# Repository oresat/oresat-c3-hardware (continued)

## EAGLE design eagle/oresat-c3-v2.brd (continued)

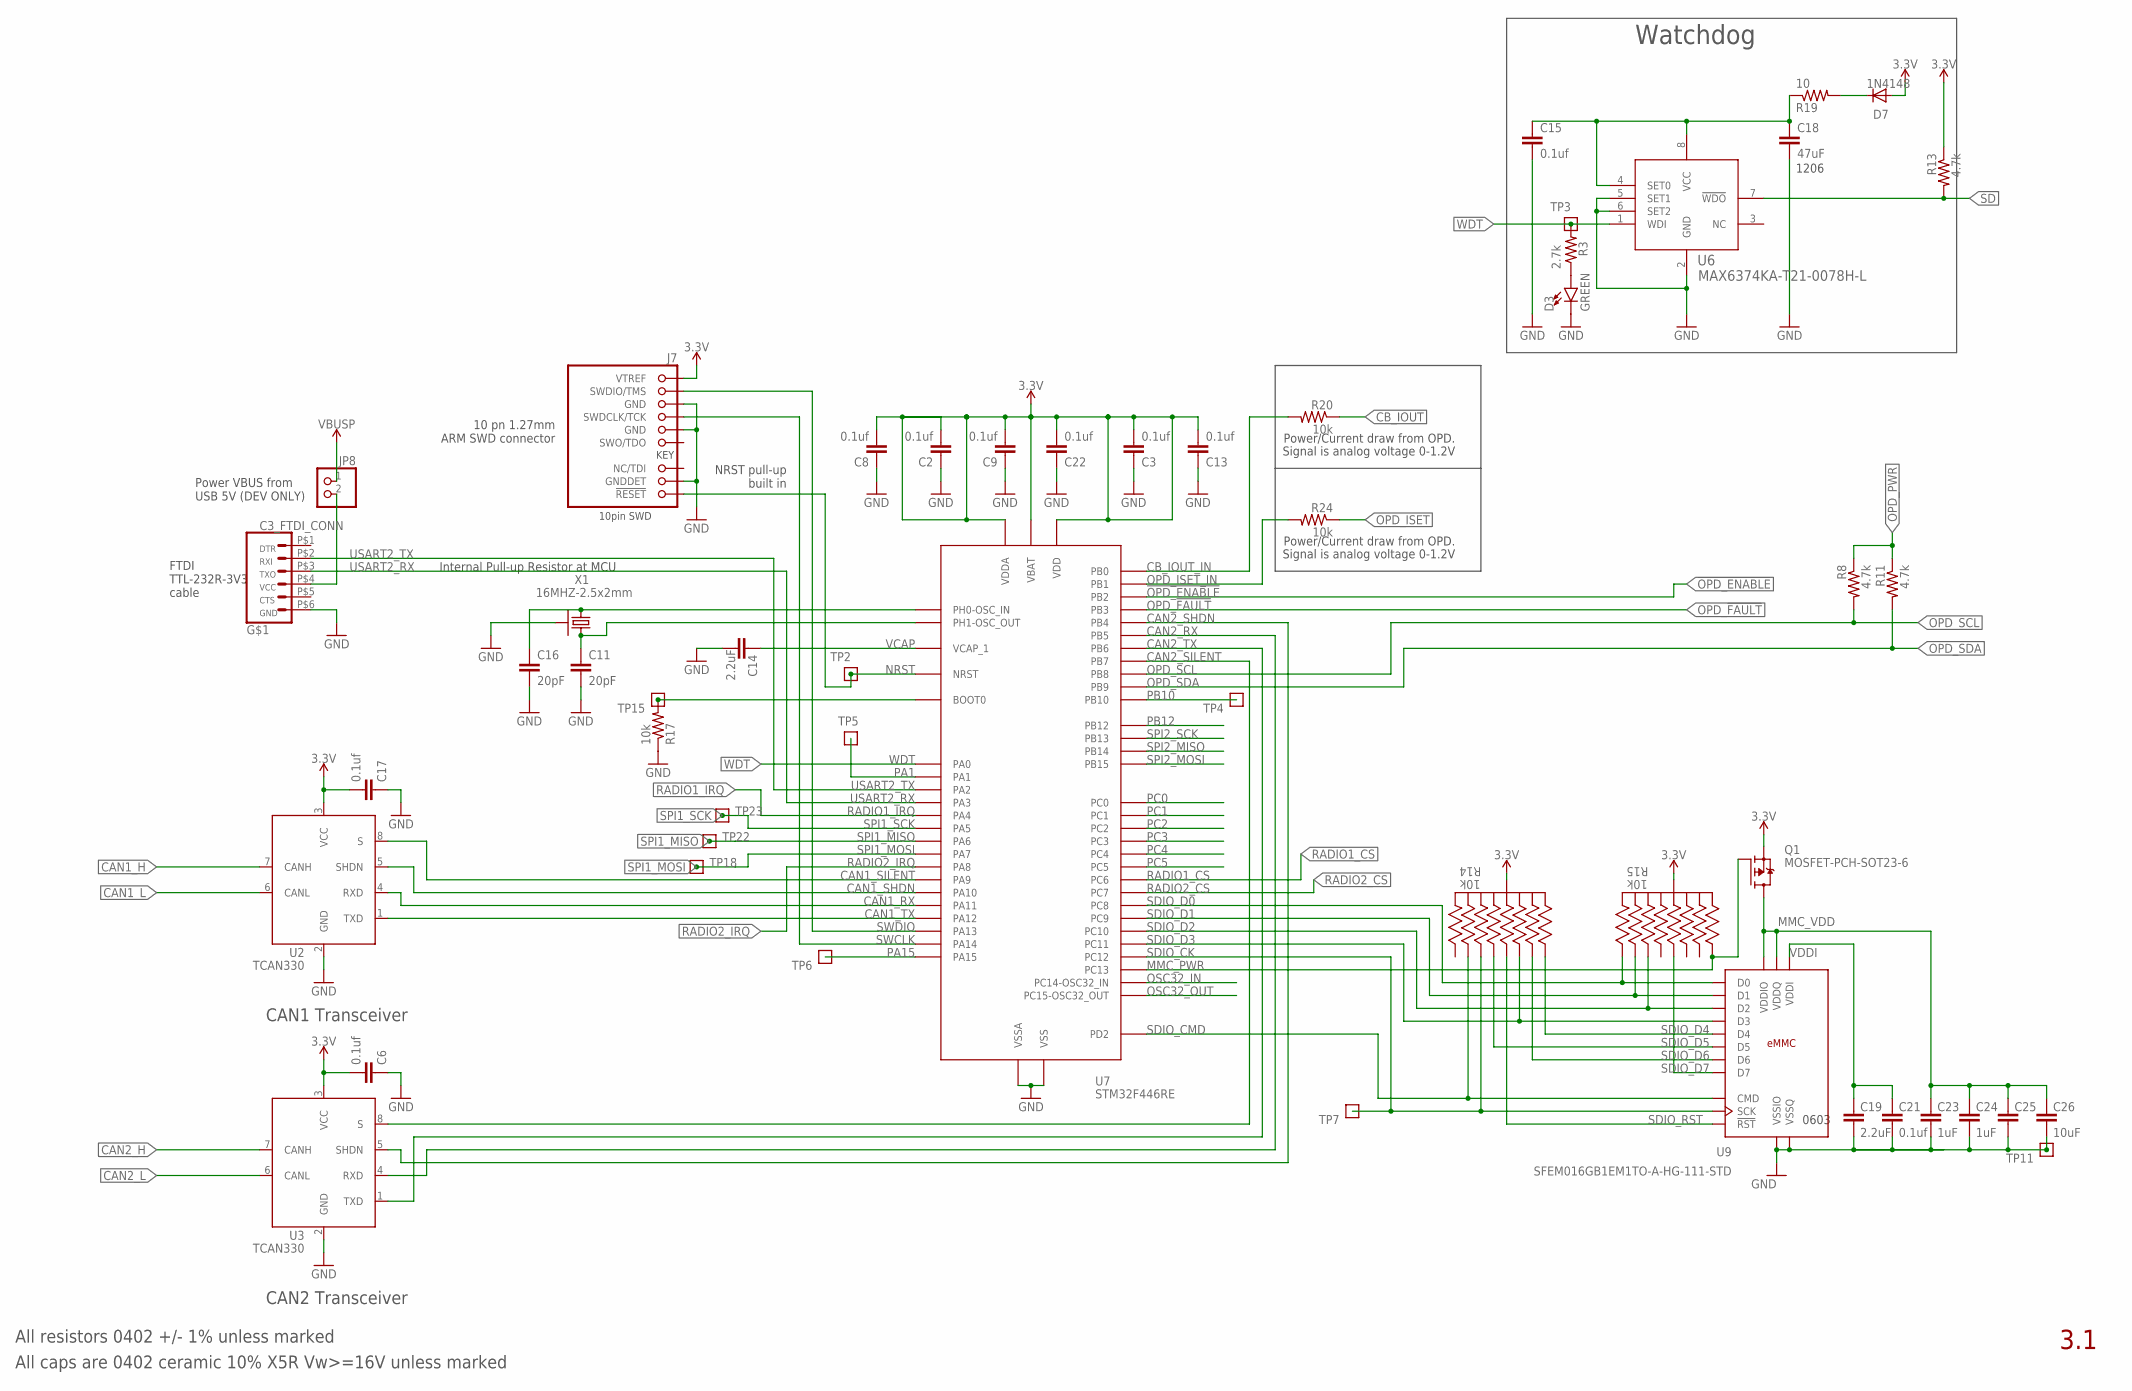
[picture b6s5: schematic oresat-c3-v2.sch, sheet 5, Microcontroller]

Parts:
C2, C3, C6, C8, C9, C13, C17, C21, C22: 0.1uf; .0603-B-NOSILK; MPN CL05B104KO5NNNC
C11, C16: 20pF; .0603-B-NOSILK; MPN CL05C200JB51PNC
C14, C19: 2.2uF; .0603-B-NOSILK; MPN CL05B104KO5NNNC
C15: 0.1uf; .0603-B-NOSILK; MPN CL05C200JB51PNC
C18: 47uF; .0603-B-NOSILK; MPN CL05C200JB51PNC
C23, C24, C25: 1uF; .0603-B-NOSILK; MPN CL05B104KO5NNNC
C26: 10uF; .0603-B-NOSILK; MPN CL05B104KO5NNNC
D3: GREEN; LED-0603
D7: 1N4148; SOD-323
J7: FTSH-105-XX-X-DV-K; CON10_2X5_DUK_FTSH; MPN FTSH-105-01-F-DV-K
JP8: PINHD-1X2; 1X02
Q1: MOSFET-PCH-SOT23-6; SOT23-6
R3: 2.7k; .0603-C-NOSILK; MPN RC1005F6653CS
R8, R11, R13: 4.7k; .0603-C-NOSILK
R14, R15: 10k; ARRAY_EXBA-M
R17: 10k; .0603-C-NOSILK; MPN RC1005F6653CS
R19: 10; .0603-C-NOSILK
R20, R24: 10k; .0603-C-NOSILK
TP2, TP3, TP4, TP5, TP6, TP7, TP11, TP15, TP18, TP22, TP23: TEST-POINT; 2MM-TEST-POINT
U2, U3: TCAN330; SOT23-8_TI-DCN; MPN TCAN330GDCNT
U6: MAX6374KA-T21-0078H-L; 21-0078H-L
U7: STM32F446RE; QFP-10X10-64
U9: SFEM016GB1EM1TO-A-HG-111-STD; BGA-153(11.5X13)(EMMC-BA)
U$2: C3_FTDI_CONN; 6_PIN_SERIAL_TARGET_SIDE_W_SILK
X1: 16MHZ-2.5x2mm; CRYSTAL_2.5X2; MPN ECS-160-10-36Q-ES-TR

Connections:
3.3V: C2.2, C3.2, C6.2, C8.2, C9.2, C13.2, C17.2, C22.2, D7.2 (A), J7.1 (VTREF), Q1.4 (S), R13.1, R14.5 (55), R14.10 (55), R15.5 (55), R15.10 (55), U2.3 (VCC), U3.3 (VCC), U7.1 (VBAT), U7.13 (VDDA), U7.19 (VDD), U7.32 (VDD), U7.48 (VDD), U7.64 (VDD); also elsewhere on the board
!OPD_ENABLE: U7.28 (PB2); also elsewhere on the board
BOOT0: R17.2, TP15.1, U7.60 (BOOT0)
CAN1_H: U2.7 (CANH); also elsewhere on the board
CAN1_L: U2.6 (CANL); also elsewhere on the board
CAN1_RX: U2.4 (RXD), U7.44 (PA11)
CAN1_SHDN: U2.5 (SHDN), U7.43 (PA10)
CAN1_SILENT: U2.8 (S), U7.42 (PA9)
CAN1_TX: U2.1 (TXD), U7.45 (PA12)
CAN2_H: U3.7 (CANH); also elsewhere on the board
CAN2_L: U3.6 (CANL); also elsewhere on the board
CAN2_RX: U3.4 (RXD), U7.57 (PB5)
CAN2_SHDN: U3.5 (SHDN), U7.56 (PB4)
CAN2_SILENT: U3.8 (S), U7.59 (PB7)
CAN2_TX: U3.1 (TXD), U7.58 (PB6)
CB_IOUT: R20.1; also elsewhere on the board
CB_IOUT_IN: R20.2, U7.26 (PB0)
CRYSTALIN: C16.1, U7.5 (PH0-OSC_IN), X1.1
CRYSTALOUT: C11.1, U7.6 (PH1-OSC_OUT), X1.3 (2)
GND: C2.1, C3.1, C6.1, C8.1, C9.1, C11.2, C13.1, C14.2, C15.2, C16.2, C17.1, C18.2, C19.2, C21.2, C22.1, C23.2, C24.2, C25.2, C26.2, D3.C, J7.3 (GND), J7.5 (GND), J7.9 (GNDDET), R17.1, TP11.1, U2.2 (GND), U3.2 (GND), U6.2 (GND), U6.5 (SET1), U6.6 (SET2), U7.12 (VSSA), U7.18 (VSS), U7.31 (VSS), U7.47 (VSS), U7.63 (VSS), U9.A6 (VSSIO), U9.C4 (VSSQ), U9.D4 (VSSIO), U9.E7 (VSSIO), U9.G5 (VSSIO), U9.H10 (VSSIO), U9.J5 (VSSIO), U9.K8 (VSSIO), U9.N1 (VSSQ), U9.N2 (VSSQ), U9.N5 (VSSQ), U9.P4 (VSSQ), U9.P6 (VSSQ), U$2.P$6 (GND), X1.2 (SHIELD), X1.4 (SHIELD); also elsewhere on the board
MMC_PWR: Q1.3 (G), R15.6 (66), U7.2 (PC13)
MMC_VDD: C23.1, C24.1, C25.1, C26.1, Q1.1 (D), Q1.2 (D), Q1.5 (D), Q1.6 (D), U9.C6 (VDDQ), U9.E6 (VDDIO), U9.F5 (VDDIO), U9.J10 (VDDIO), U9.K9 (VDDIO), U9.M4 (VDDQ), U9.N4 (VDDQ), U9.P3 (VDDQ), U9.P5 (VDDQ)
unnamed: D3.A, R3.1
unnamed: D7.1 (C), R19.2
unnamed: JP8.2, U$2.P$4 (VCC)
NRST: J7.10 (!RESET), TP2.1, U7.7 (NRST)
OPD_!FAULT: U7.55 (PB3); also elsewhere on the board
OPD_ISET: R24.1; also elsewhere on the board
OPD_ISET_IN: R24.2, U7.27 (PB1)
OPD_PWR: R8.1, R11.1; also elsewhere on the board
OPD_SCL: R8.2, U7.61 (PB8); also elsewhere on the board
OPD_SDA: R11.2, U7.62 (PB9); also elsewhere on the board
OSC32_IN: U7.3 (PC14-OSC32_IN)
OSC32_OUT: U7.4 (PC15-OSC32_OUT)
PA1: TP5.1, U7.15 (PA1)
PA15: TP6.1, U7.50 (PA15)
PB10: TP4.1, U7.29 (PB10)
PB12: U7.33 (PB12)
PC0: U7.8 (PC0)
PC1: U7.9 (PC1)
PC2: U7.10 (PC2)
PC3: U7.11 (PC3)
PC4: U7.24 (PC4)
PC5: U7.25 (PC5)
RADIO1_CS: U7.37 (PC6); also elsewhere on the board
RADIO1_IRQ: U7.20 (PA4); also elsewhere on the board
RADIO2_CS: U7.38 (PC7); also elsewhere on the board
RADIO2_IRQ: U7.41 (PA8); also elsewhere on the board
SD: R13.2, U6.7 (!WDO); also elsewhere on the board
SDIO_CK: R14.2 (22), TP7.1, U7.53 (PC12), U9.M6 (SCK)
SDIO_CMD: R14.9 (99), U7.54 (PD2), U9.M5 (CMD)
SDIO_D0: R15.1 (11), U7.39 (PC8), U9.A3 (D0)
SDIO_D1: R15.9 (99), U7.40 (PC9), U9.A4 (D1)
SDIO_D2: R15.2 (22), U7.51 (PC10), U9.A5 (D2)
SDIO_D3: R14.7 (77), U7.52 (PC11), U9.A1 (D3), U9.B2 (D3)
SDIO_D4: R14.6 (66), U9.A2 (D4), U9.B3 (D4)
SDIO_D5: R14.8 (88), U9.B4 (D5), U9.C3 (D5), U9.D3 (D5)
SDIO_D6: R14.4 (44), U9.B5 (D6), U9.C5 (D6)
SDIO_D7: R15.3 (33), U9.B6 (D7), U9.C7 (D7)
SDIO_RST: R14.3 (33), U9.K5 (!RST!)
SPI1_MISO: TP22.1, U7.22 (PA6); also elsewhere on the board
SPI1_MOSI: TP18.1, U7.23 (PA7); also elsewhere on the board
SPI1_SCK: TP23.1, U7.21 (PA5); also elsewhere on the board
SPI2_MISO: U7.35 (PB14)
SPI2_MOSI: U7.36 (PB15)
SPI2_SCK: U7.34 (PB13)
SWCLK: J7.4 (SWDCLK/TCK), U7.49 (PA14)
SWDIO: J7.2 (SWDIO/TMS), U7.46 (PA13)
USART2_RX: U7.17 (PA3), U$2.P$3 (TXO)
USART2_TX: U7.16 (PA2), U$2.P$2 (RXI)
VBUSP: JP8.1; also elsewhere on the board
VCAP: C14.1, U7.30 (VCAP_1)
VDDI: C19.1, C21.1, U9.C1 (VDDI), U9.C2 (VDDI)
WDT: R3.2, TP3.1, U6.1 (WDI), U7.14 (PA0)
WDT-PWR: C15.1, C18.1, R19.1, U6.4 (SET0), U6.8 (VCC)

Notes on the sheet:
NRST pull-up built in
FTDI TTL-232R-3V3 cable
Power VBUS from USB 5V (DEV ONLY)
10 pn 1.27mm ARM SWD connector
CAN1 Transceiver
3.1
Power/Current draw from OPD.
Signal is analog voltage 0-1.2V
CAN2 Transceiver
Watchdog
Internal Pull-up Resistor at MCU
All resistors 0402 +/- 1% unless marked
All caps are 0402 ceramic 10% X5R Vw>=16V unless marked
1206
0603

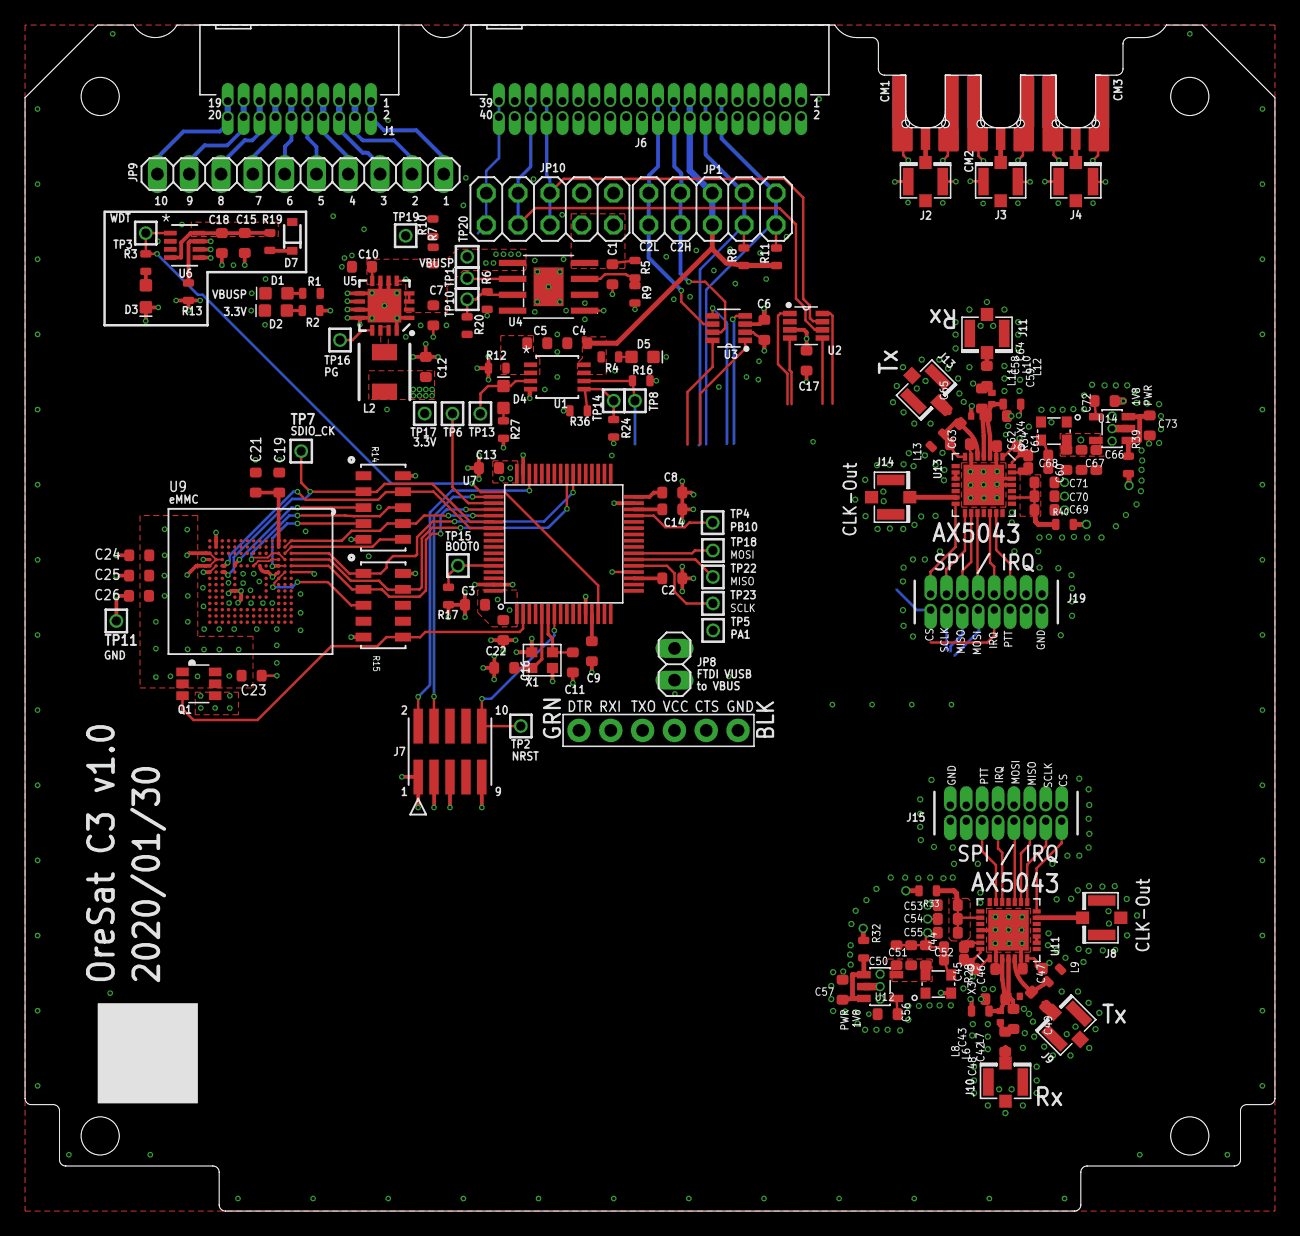
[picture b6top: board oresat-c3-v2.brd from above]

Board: 4 copper layers, 99.8 x 94.7 mm, 163 parts (0 on the bottom side), 133 nets.

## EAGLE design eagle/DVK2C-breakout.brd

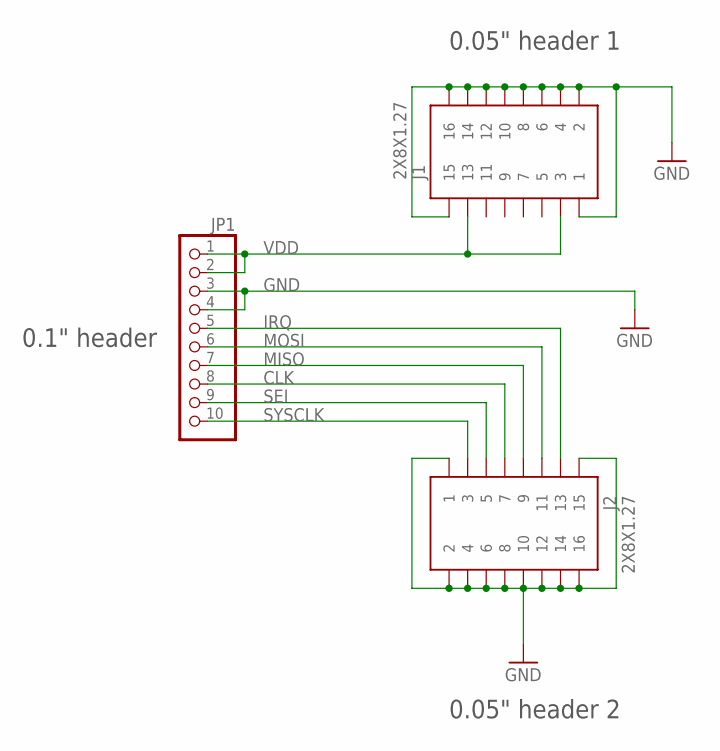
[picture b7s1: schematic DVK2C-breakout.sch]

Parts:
J1, J2: 2X8X1.27
JP1: PINHD-1X10; 1X10

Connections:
CLK: J2.7, JP1.8
GND: J1.1, J1.2, J1.4, J1.6, J1.8, J1.10, J1.12, J1.14, J1.15, J1.16, J2.1, J2.2, J2.4, J2.6, J2.8, J2.10, J2.12, J2.14, J2.15, J2.16, JP1.3, JP1.4
IRQ: J2.13, JP1.5
MISO: J2.9, JP1.7
MOSI: J2.11, JP1.6
SEI: J2.5, JP1.9
SYSCLK: J2.3, JP1.10
VDD: J1.3, J1.13, JP1.1, JP1.2

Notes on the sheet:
0.1" header
0.05" header 1
0.05" header 2

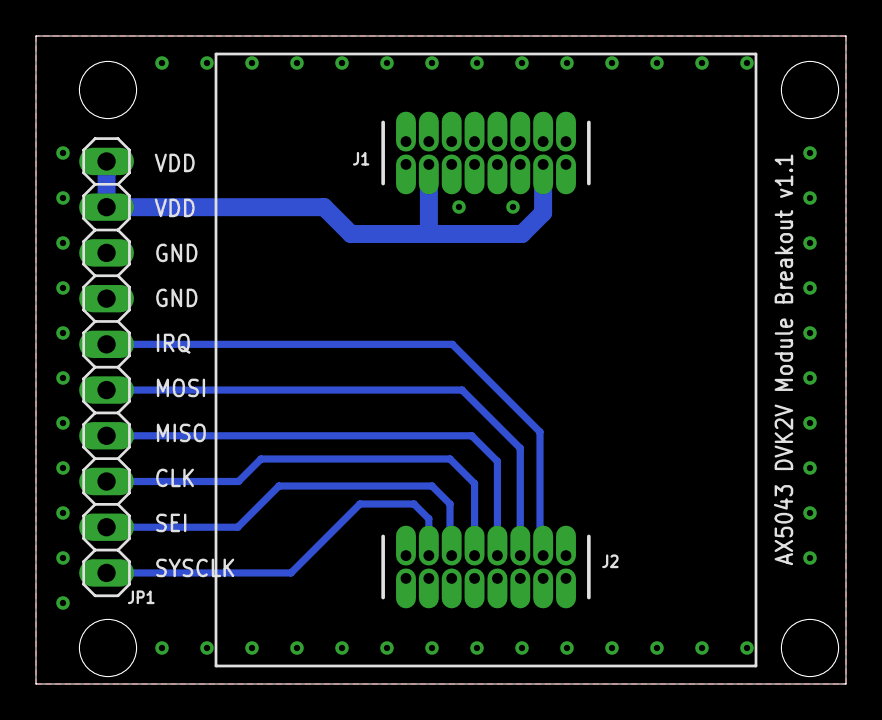
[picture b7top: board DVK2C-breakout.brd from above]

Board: 2 copper layers, 45.0 x 36.0 mm, 3 parts (0 on the bottom side), 8 nets.

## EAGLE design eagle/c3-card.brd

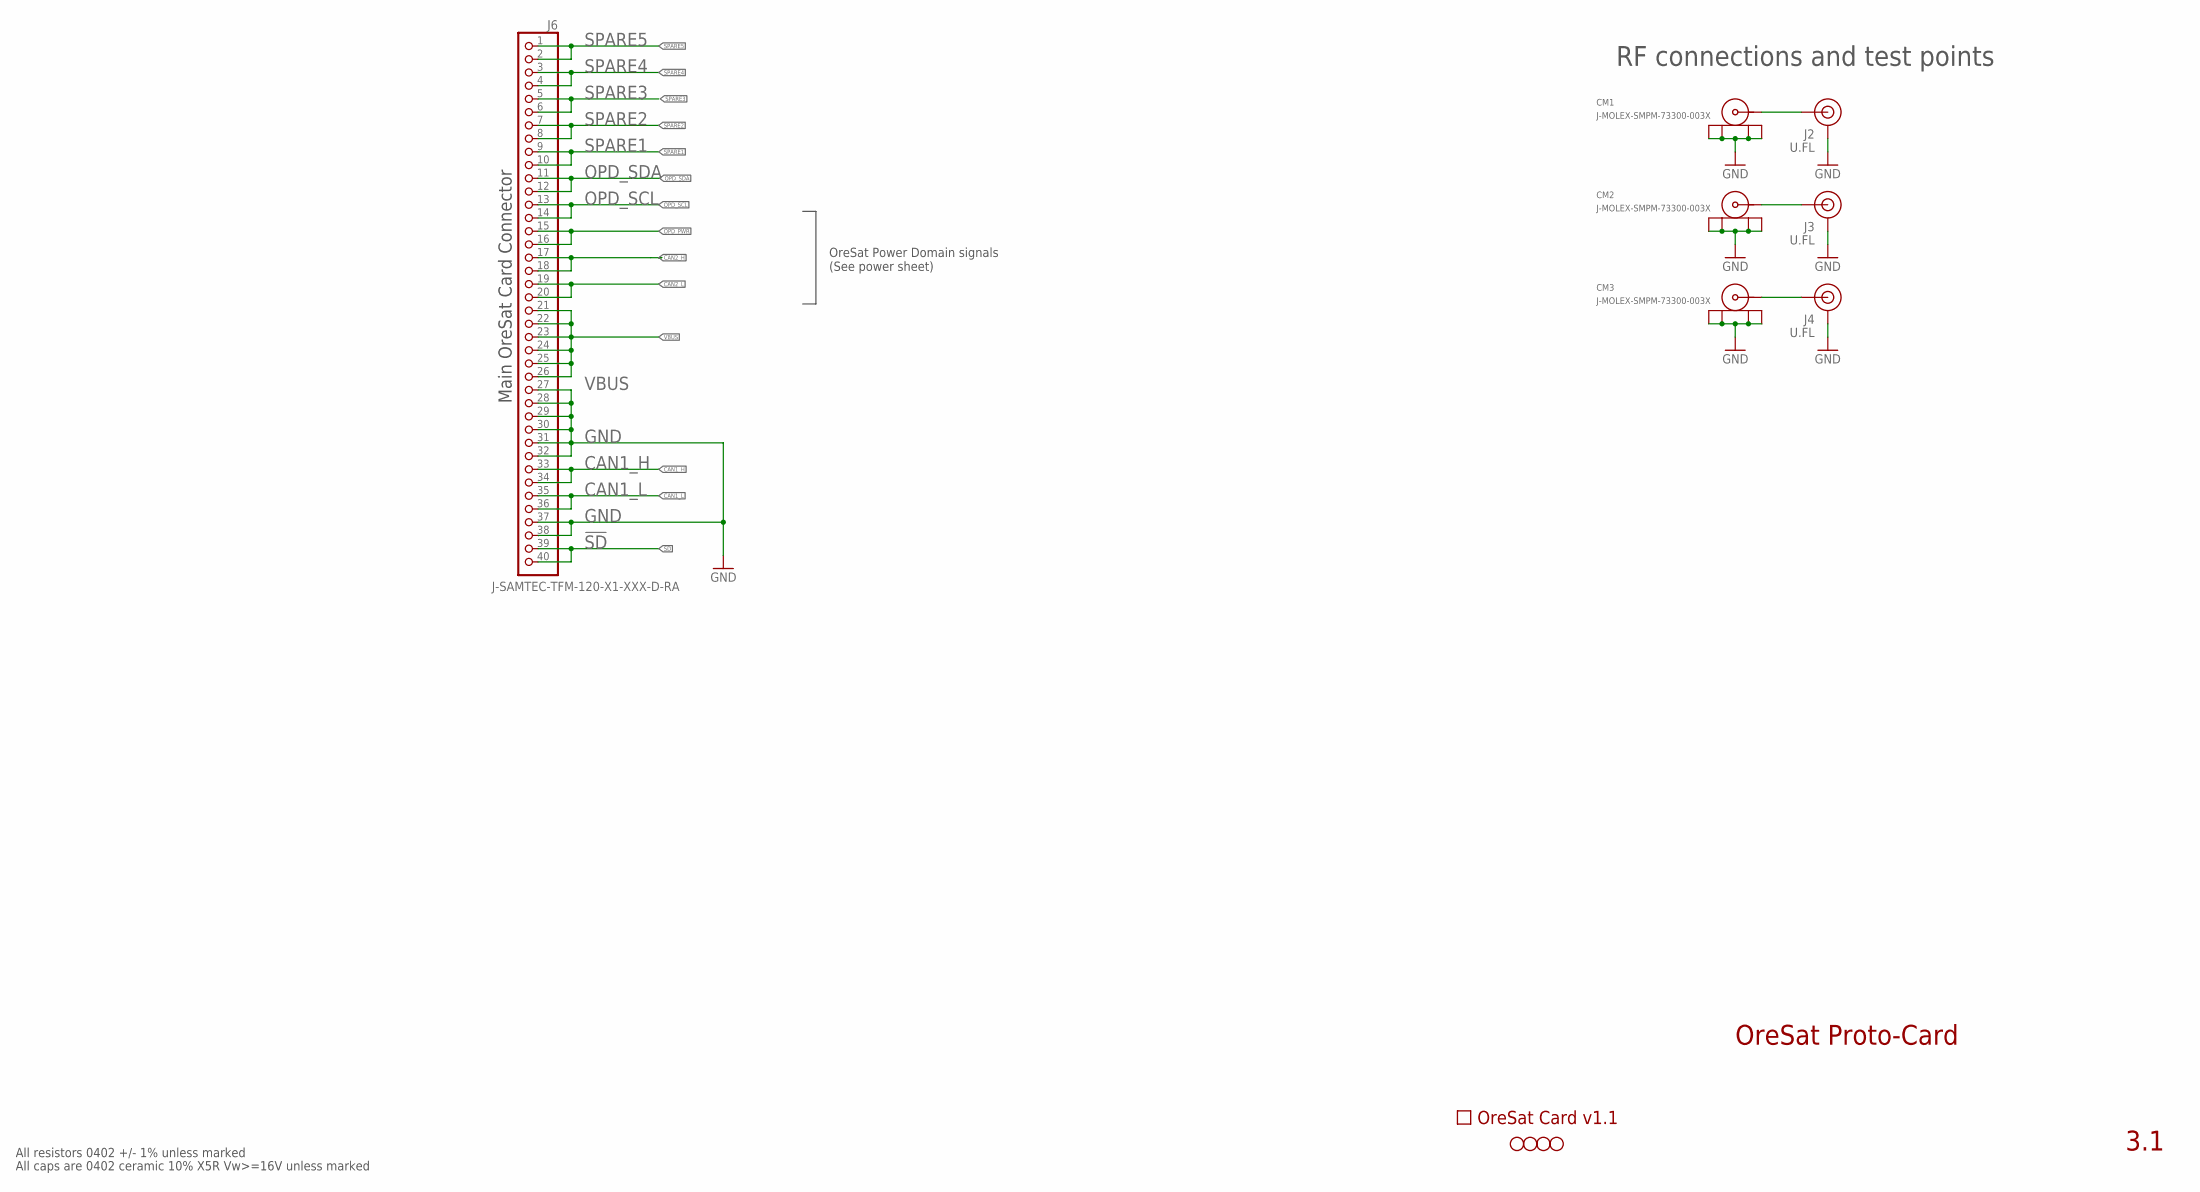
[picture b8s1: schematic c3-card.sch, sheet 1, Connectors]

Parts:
CM1, CM2, CM3: J-MOLEX-SMPM-73300-003X; J-MOLEX-SMPM-073300-003X; MPN 73300-0020
H1, H2, H3, H4: STAND-OFFTIGHT; STAND-OFF-TIGHT
J2, J3, J4: U.FL
J6: J-SAMTEC-TFM-120-X1-XXX-D-RA; MPN TFM-120-01-L-D-RA
U$2: ORESAT-CARD-V1.1-3XRF

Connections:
!SD: J6.39, J6.40
CAN1_H: J6.33, J6.34; also elsewhere on the board
CAN1_L: J6.35, J6.36; also elsewhere on the board
CAN2_H: J6.17, J6.18; also elsewhere on the board
CAN2_L: J6.19, J6.20; also elsewhere on the board
GND: CM1.P$1 (SHIELD3), CM1.P$2 (SHIELD2), CM1.P$3 (SHIELD1), CM1.P$4 (SHIELD), CM2.P$1 (SHIELD3), CM2.P$2 (SHIELD2), CM2.P$3 (SHIELD1), CM2.P$4 (SHIELD), CM3.P$1 (SHIELD3), CM3.P$2 (SHIELD2), CM3.P$3 (SHIELD1), CM3.P$4 (SHIELD), J2.1 (GND), J2.2 (GND), J3.1 (GND), J3.2 (GND), J4.1 (GND), J4.2 (GND), J6.27, J6.28, J6.29, J6.30, J6.31, J6.32, J6.37, J6.38; also elsewhere on the board
unnamed: CM3.RF (CENTER), J4.FEED (SIGNAL)
OPD_PWR: J6.15, J6.16
OPD_SCL: J6.13, J6.14
OPD_SDA: J6.11, J6.12
RF1: CM1.RF (CENTER), J2.FEED (SIGNAL)
RF2: CM2.RF (CENTER), J3.FEED (SIGNAL)
SPARE1: J6.9, J6.10
SPARE2: J6.7, J6.8
SPARE3: J6.5, J6.6
SPARE4: J6.3, J6.4
SPARE5: J6.1, J6.2
VBUS: J6.21, J6.22, J6.23, J6.24, J6.25, J6.26; also elsewhere on the board

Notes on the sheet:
OreSat Proto-Card
3.1
All resistors 0402 +/- 1% unless marked
All caps are 0402 ceramic 10% X5R Vw>=16V unless marked
Main OreSat Card Connector
RF connections and test points
OreSat Power Domain signals (See power sheet)

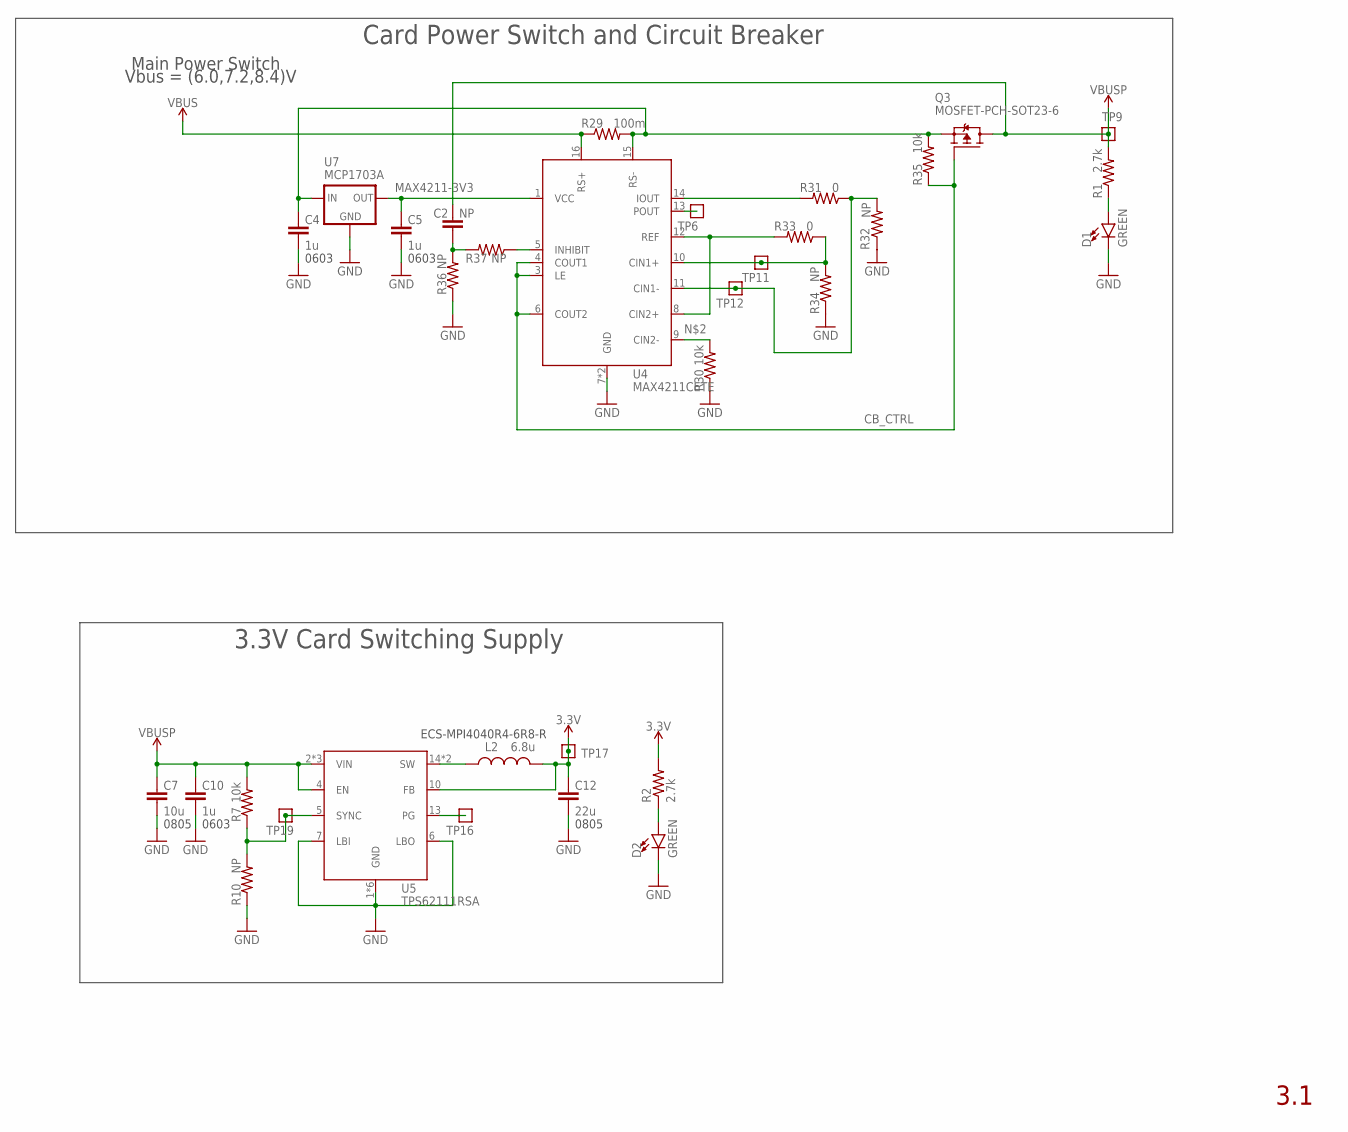
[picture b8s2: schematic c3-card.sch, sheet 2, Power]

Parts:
C2: NP; .0402-B-NOSILK; MPN CL05B104KO5NNNC
C4, C5, C10: 1u; .0603-B-NOSILK; MPN CL05B104KO5NNNC
C7: 10u; .0805-B-NOSILK
C12: 22u; .0805-B-NOSILK
D1, D2: GREEN; LED-0603
L2: 6.8u; ECS-MPI4040; MPN ECS-MPI4040R4-6R8-R
Q3: MOSFET-PCH-SOT23-6; SOT23-6; MPN DMP3050LVT-7
R1, R2: 2.7k; .0402-B-NOSILK; MPN RC1005F6653CS
R7, R30, R35: 10k; .0402-B-NOSILK; MPN RC1005F6653CS
R10, R32, R34, R36, R37: NP; .0402-B-NOSILK; MPN RC1005F6653CS
R29: 100m; R1206
R31, R33: 0; .0402-B-NOSILK; MPN RC1005F6653CS
TP6, TP9, TP11, TP12, TP16, TP17, TP19: TEST-POINT; 2MM-TEST-POINT
U4: MAX4211CETE; QFN65P400X400X80-17T210; MPN MAX4211CETE
U5: TPS62111RSA; S-PVQFN-16; MPN TPS62111RSA
U7: MCP1703A; SOT23; MPN MCP1703AT-3302E/CB

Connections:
3.3V: C12.1, L2.2, R2.2, TP17.1, U5.10 (FB); also elsewhere on the board
CB_CTRL: Q3.3 (G), R35.1, U4.3 (LE), U4.4 (COUT1), U4.6 (COUT2)
GND: C4.2, C5.2, C7.2, C10.2, C12.2, D1.C, D2.C, R10.1, R30.1, R32.1, R34.1, R36.1, U4.7 (GND), U4.EPAD (GND), U5.1 (GND), U5.6 (LBO), U5.7 (LBI), U5.9 (GND), U5.11 (GND), U5.12 (GND), U5.16 (GND), U5.PAD (GND), U7.1 (GND); also elsewhere on the board
MAX4211-3V3: C5.1, U4.1 (VCC), U7.2 (OUT)
unnamed: R30.2, U4.9 (CIN2-)
unnamed: D1.A, R1.1
unnamed: D2.A, R2.1
unnamed: C4.1, Q3.4 (S), R29.2, R35.2, U4.15 (RS-), U7.3 (IN)
unnamed: R31.1, R32.2, TP12.1, U4.11 (CIN1-)
unnamed: R33.1, R34.2, TP11.1, U4.10 (CIN1+)
unnamed: R31.2, U4.14 (IOUT)
unnamed: R33.2, U4.8 (CIN2+), U4.12 (REF)
unnamed: TP6.1, U4.13 (POUT)
unnamed: C2.1, R36.2, R37.2
unnamed: R37.1, U4.5 (INHIBIT)
TPS62111-PG: TP16.1, U5.13 (PG)
TPS62111-SYNC: R7.1, R10.2, TP19.1, U5.5 (SYNC)
TPS62111_SW: L2.1, U5.14 (SW), U5.15 (SW)
VBUS: R29.1, U4.16 (RS+); also elsewhere on the board
VBUSP: C2.2, C7.1, C10.1, Q3.1 (D), Q3.2 (D), Q3.5 (D), Q3.6 (D), R1.2, R7.2, TP9.1, U5.2 (VIN), U5.3 (VIN), U5.4 (EN), U5.8 (VIN)

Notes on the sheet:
Main Power Switch
0805
0603
ECS-MPI4040R4-6R8-R
Vbus = (6.0,7.2,8.4)V
3.3V Card Switching Supply
Card Power Switch and Circuit Breaker
3.1

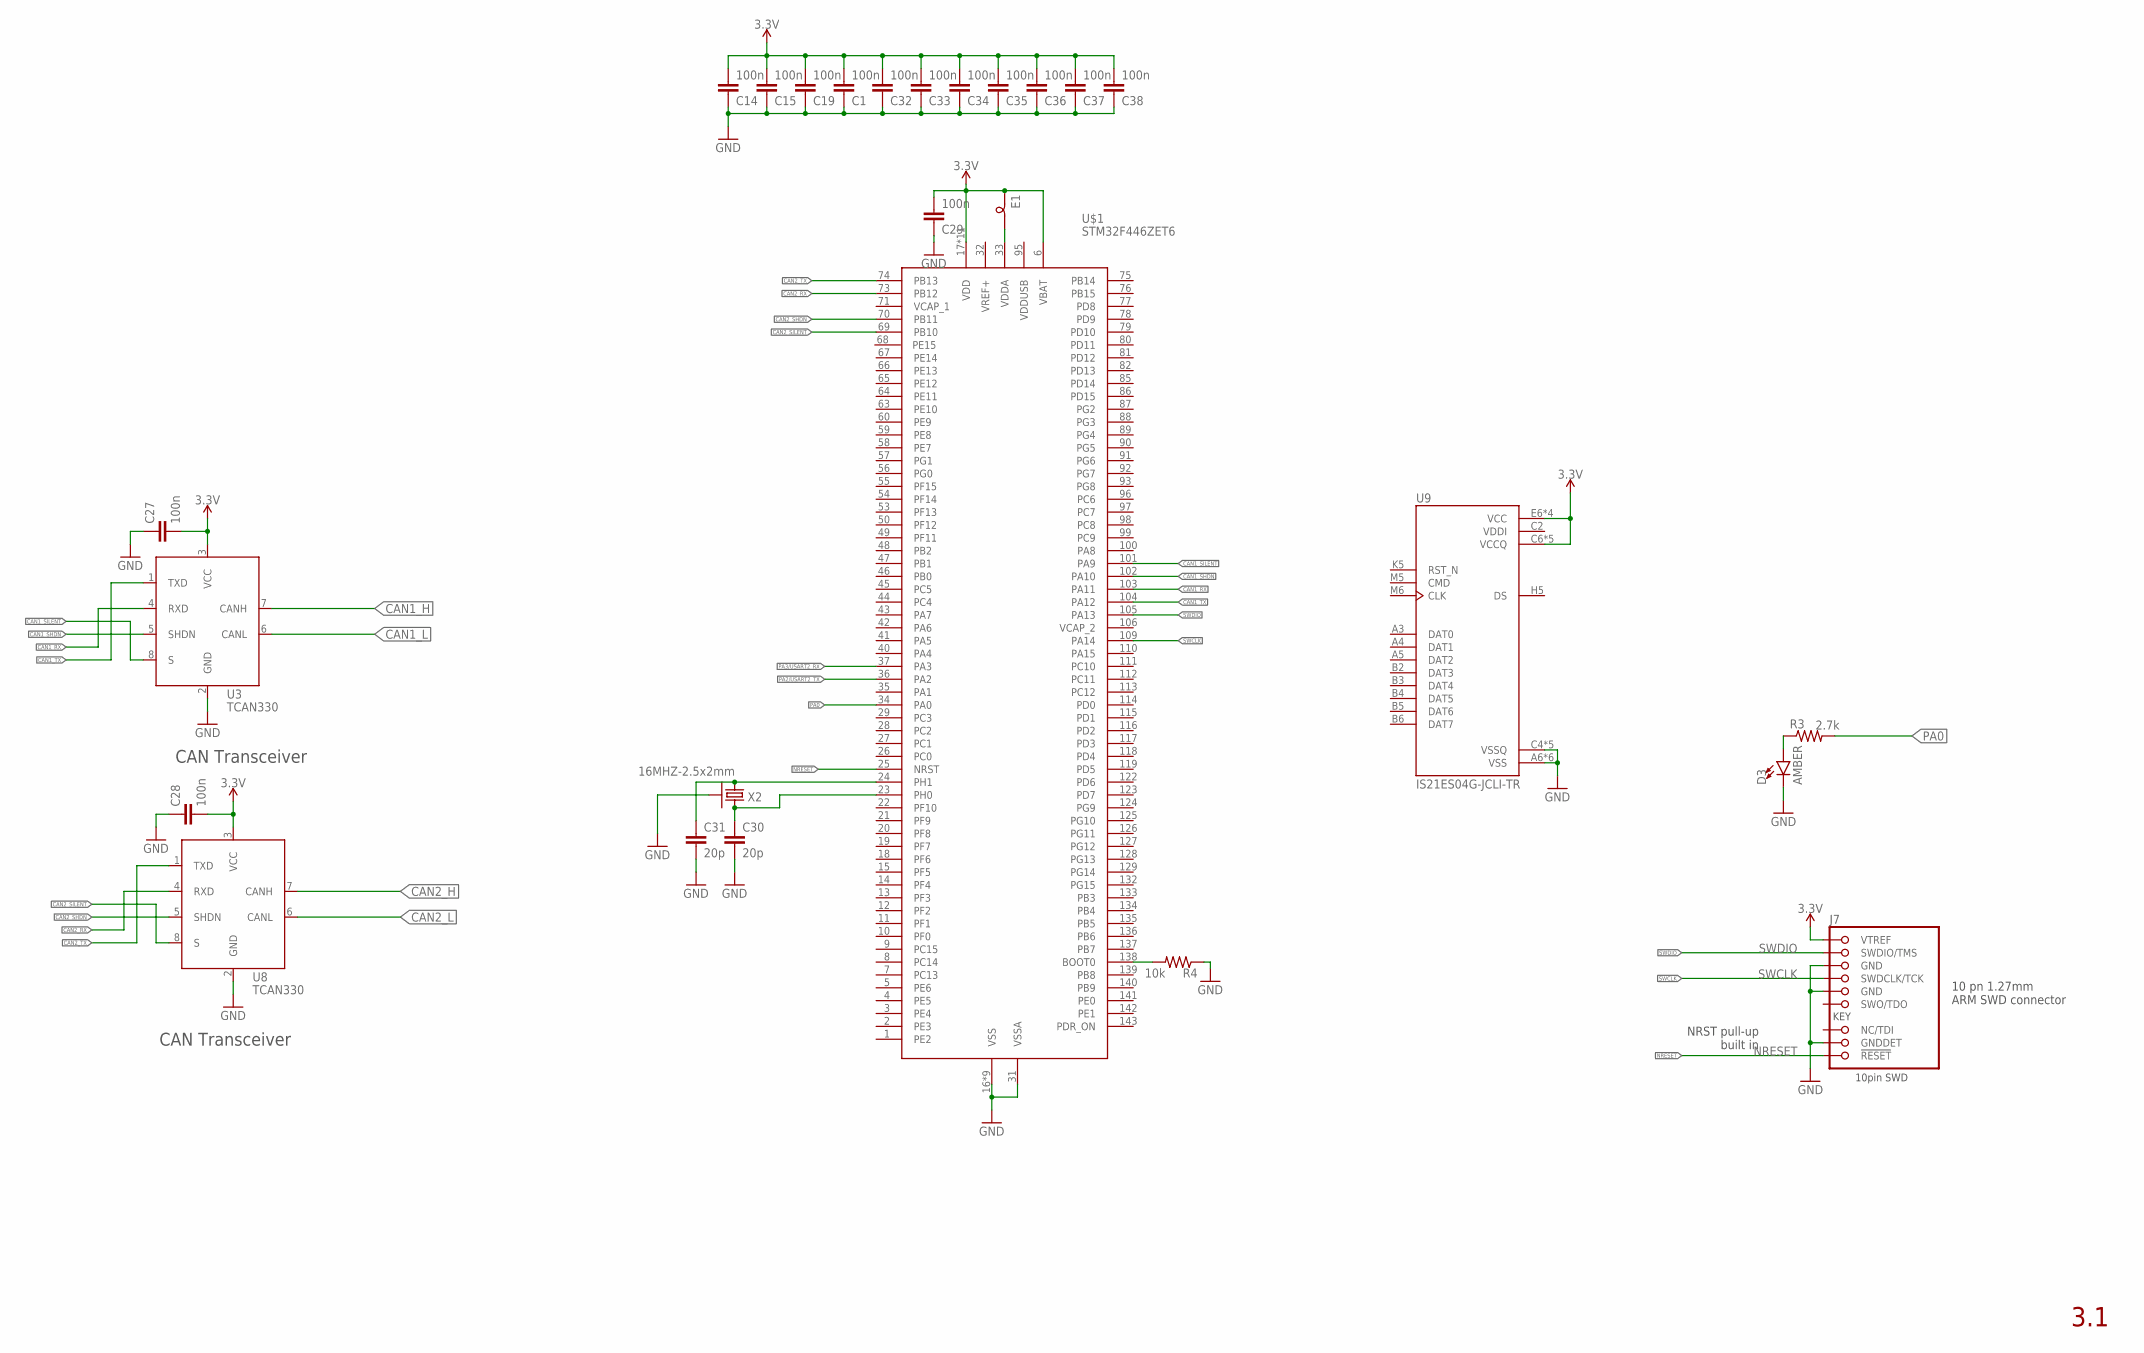
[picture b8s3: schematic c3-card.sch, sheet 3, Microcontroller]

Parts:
C1, C14, C15, C19, C27, C28, C29, C32, C33, C34, C35, C36, C37, C38: 100n; .0402-B-NOSILK; MPN CL05B104KO5NNNC
C30, C31: 20p; .0402-B-NOSILK; MPN CL05C200JB51PNC
D3: AMBER; LED-0603
E1: L-BEAD-0603-B; .0603-B
J7: FTSH-105-XX-X-DV-K; CON10_2X5_DUK_FTSH; MPN FTSH-105-01-F-DV-K
R3: 2.7k; .0402-B-NOSILK; MPN RC1005F6653CS
R4: 10k; .0402-B-NOSILK; MPN RC1005F6653CS
U3, U8: TCAN330; SOT23-8_TI-DCN; MPN TCAN330GDCNT
U9: IS21ES04G-JCLI-TR; BGA153N50P14X14_1150X1300X100
U$1: STM32F446ZET6; P-TQFP-144-19
X2: 16MHZ-2.5x2mm; CRYSTAL_2.5X2; MPN ECS-160-10-36Q-ES-TR

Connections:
3.3V: C1.2, C14.2, C15.2, C19.2, C27.2, C28.2, C29.2, C32.2, C33.2, C34.2, C35.2, C36.2, C37.2, C38.2, E1.1, J7.1 (VTREF), U3.3 (VCC), U8.3 (VCC), U9.C6 (VCCQ), U9.E6 (VCC), U9.F5 (VCC), U9.J10 (VCC), U9.K9 (VCC), U9.M4 (VCCQ), U9.N4 (VCCQ), U9.P3 (VCCQ), U9.P5 (VCCQ), U$1.6 (VBAT), U$1.17 (VDD), U$1.30 (VDD), U$1.39 (VDD), U$1.52 (VDD), U$1.62 (VDD), U$1.72 (VDD), U$1.84 (VDD), U$1.108 (VDD), U$1.121 (VDD), U$1.131 (VDD), U$1.144 (VDD); also elsewhere on the board
CAN1_H: U3.7 (CANH); also elsewhere on the board
CAN1_L: U3.6 (CANL); also elsewhere on the board
CAN1_RX: U3.4 (RXD), U$1.103 (PA11)
CAN1_SHDN: U3.5 (SHDN), U$1.102 (PA10)
CAN1_SILENT: U3.8 (S), U$1.101 (PA9)
CAN1_TX: U3.1 (TXD), U$1.104 (PA12)
CAN2_H: U8.7 (CANH); also elsewhere on the board
CAN2_L: U8.6 (CANL); also elsewhere on the board
CAN2_RX: U8.4 (RXD), U$1.73 (PB12)
CAN2_SHDN: U8.5 (SHDN), U$1.70 (PB11)
CAN2_SILENT: U8.8 (S), U$1.69 (PB10)
CAN2_TX: U8.1 (TXD), U$1.74 (PB13)
CRYSTALIN1: C31.1, U$1.24 (PH1), X2.1
CRYSTALOUT1: C30.1, U$1.23 (PH0), X2.3 (2)
GND: C1.1, C14.1, C15.1, C19.1, C27.1, C28.1, C29.1, C30.2, C31.2, C32.1, C33.1, C34.1, C35.1, C36.1, C37.1, C38.1, D3.C, J7.3 (GND), J7.5 (GND), J7.9 (GNDDET), R4.1, U3.2 (GND), U8.2 (GND), U9.A6 (VSS), U9.C4 (VSSQ), U9.E7 (VSS), U9.G5 (VSS), U9.H10 (VSS), U9.J5 (VSS), U9.K8 (VSS), U9.N2 (VSSQ), U9.N5 (VSSQ), U9.P4 (VSSQ), U9.P6 (VSSQ), U$1.16 (VSS), U$1.31 (VSSA), U$1.38 (VSS), U$1.51 (VSS), U$1.61 (VSS), U$1.83 (VSS), U$1.94 (VSS), U$1.107 (VSS), U$1.120 (VSS), U$1.130 (VSS), X2.2 (SHIELD), X2.4 (SHIELD); also elsewhere on the board
unnamed: D3.A, R3.1
unnamed: R4.2, U$1.138 (BOOT0)
unnamed: E1.2, U$1.33 (VDDA)
NRESET: J7.10 (!RESET), U$1.25 (NRST)
PA0: R3.2, U$1.34 (PA0)
PA2/USART2_TX: U$1.36 (PA2)
PA3/USART2_RX: U$1.37 (PA3)
SWCLK: J7.4 (SWDCLK/TCK), U$1.109 (PA14)
SWDIO: J7.2 (SWDIO/TMS), U$1.105 (PA13)
VDDI: U9.C2 (VDDI)

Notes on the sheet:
NRST pull-up built in
10 pn 1.27mm ARM SWD connector
3.1
CAN Transceiver

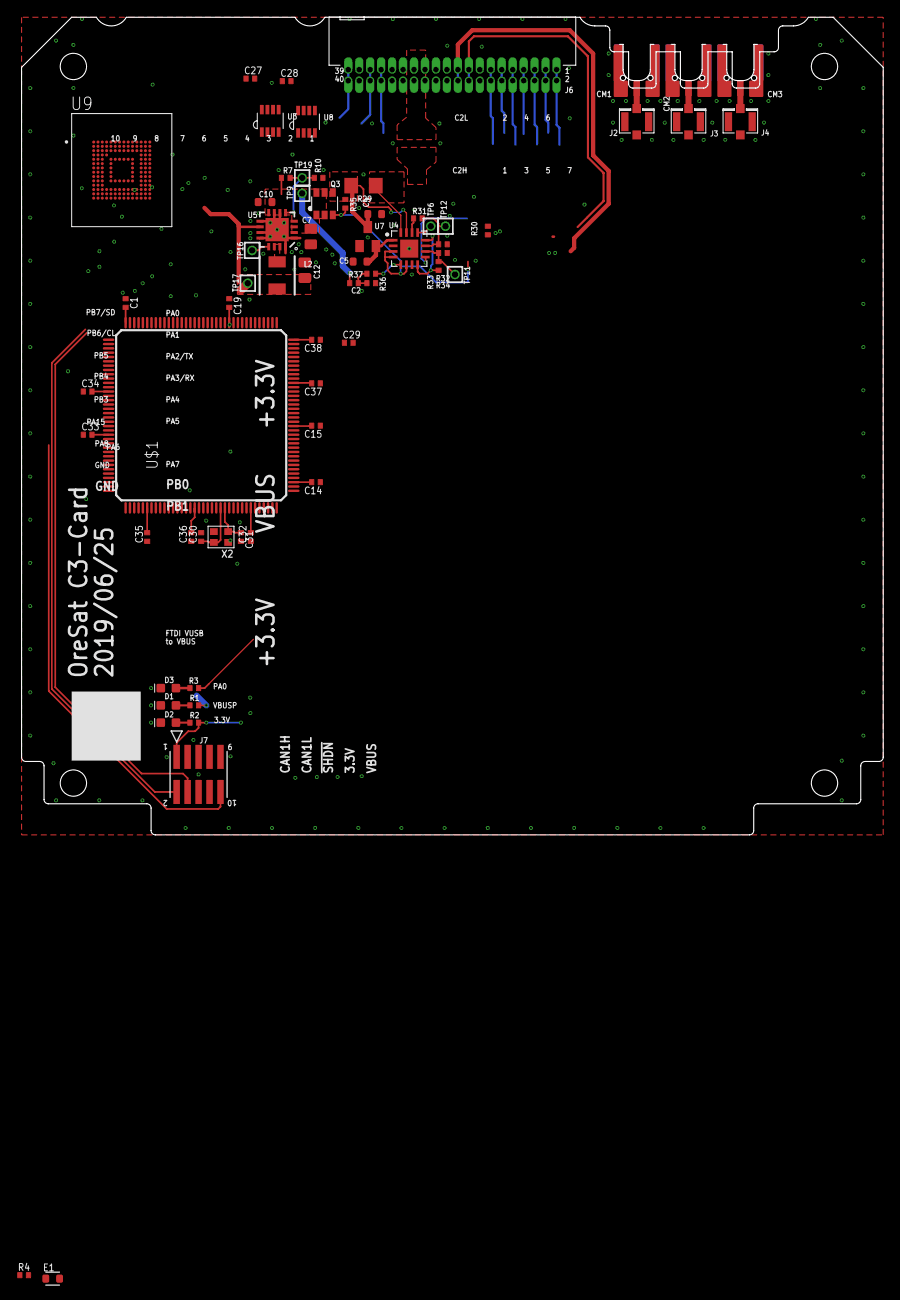
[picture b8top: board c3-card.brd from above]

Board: 4 copper layers, 99.8 x 94.7 mm, 71 parts (0 on the bottom side), 53 nets.
